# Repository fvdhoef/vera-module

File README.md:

# VERA module - Video Embedded Retro Adapter
This repository contains the files related to the VERA module. This module is developed for the Commander X16 computer by The 8-Bit Guy.

**NOTE**: The Commander X16 logo is part of the Commander X16 project and should not be used when the module is used with other projects.

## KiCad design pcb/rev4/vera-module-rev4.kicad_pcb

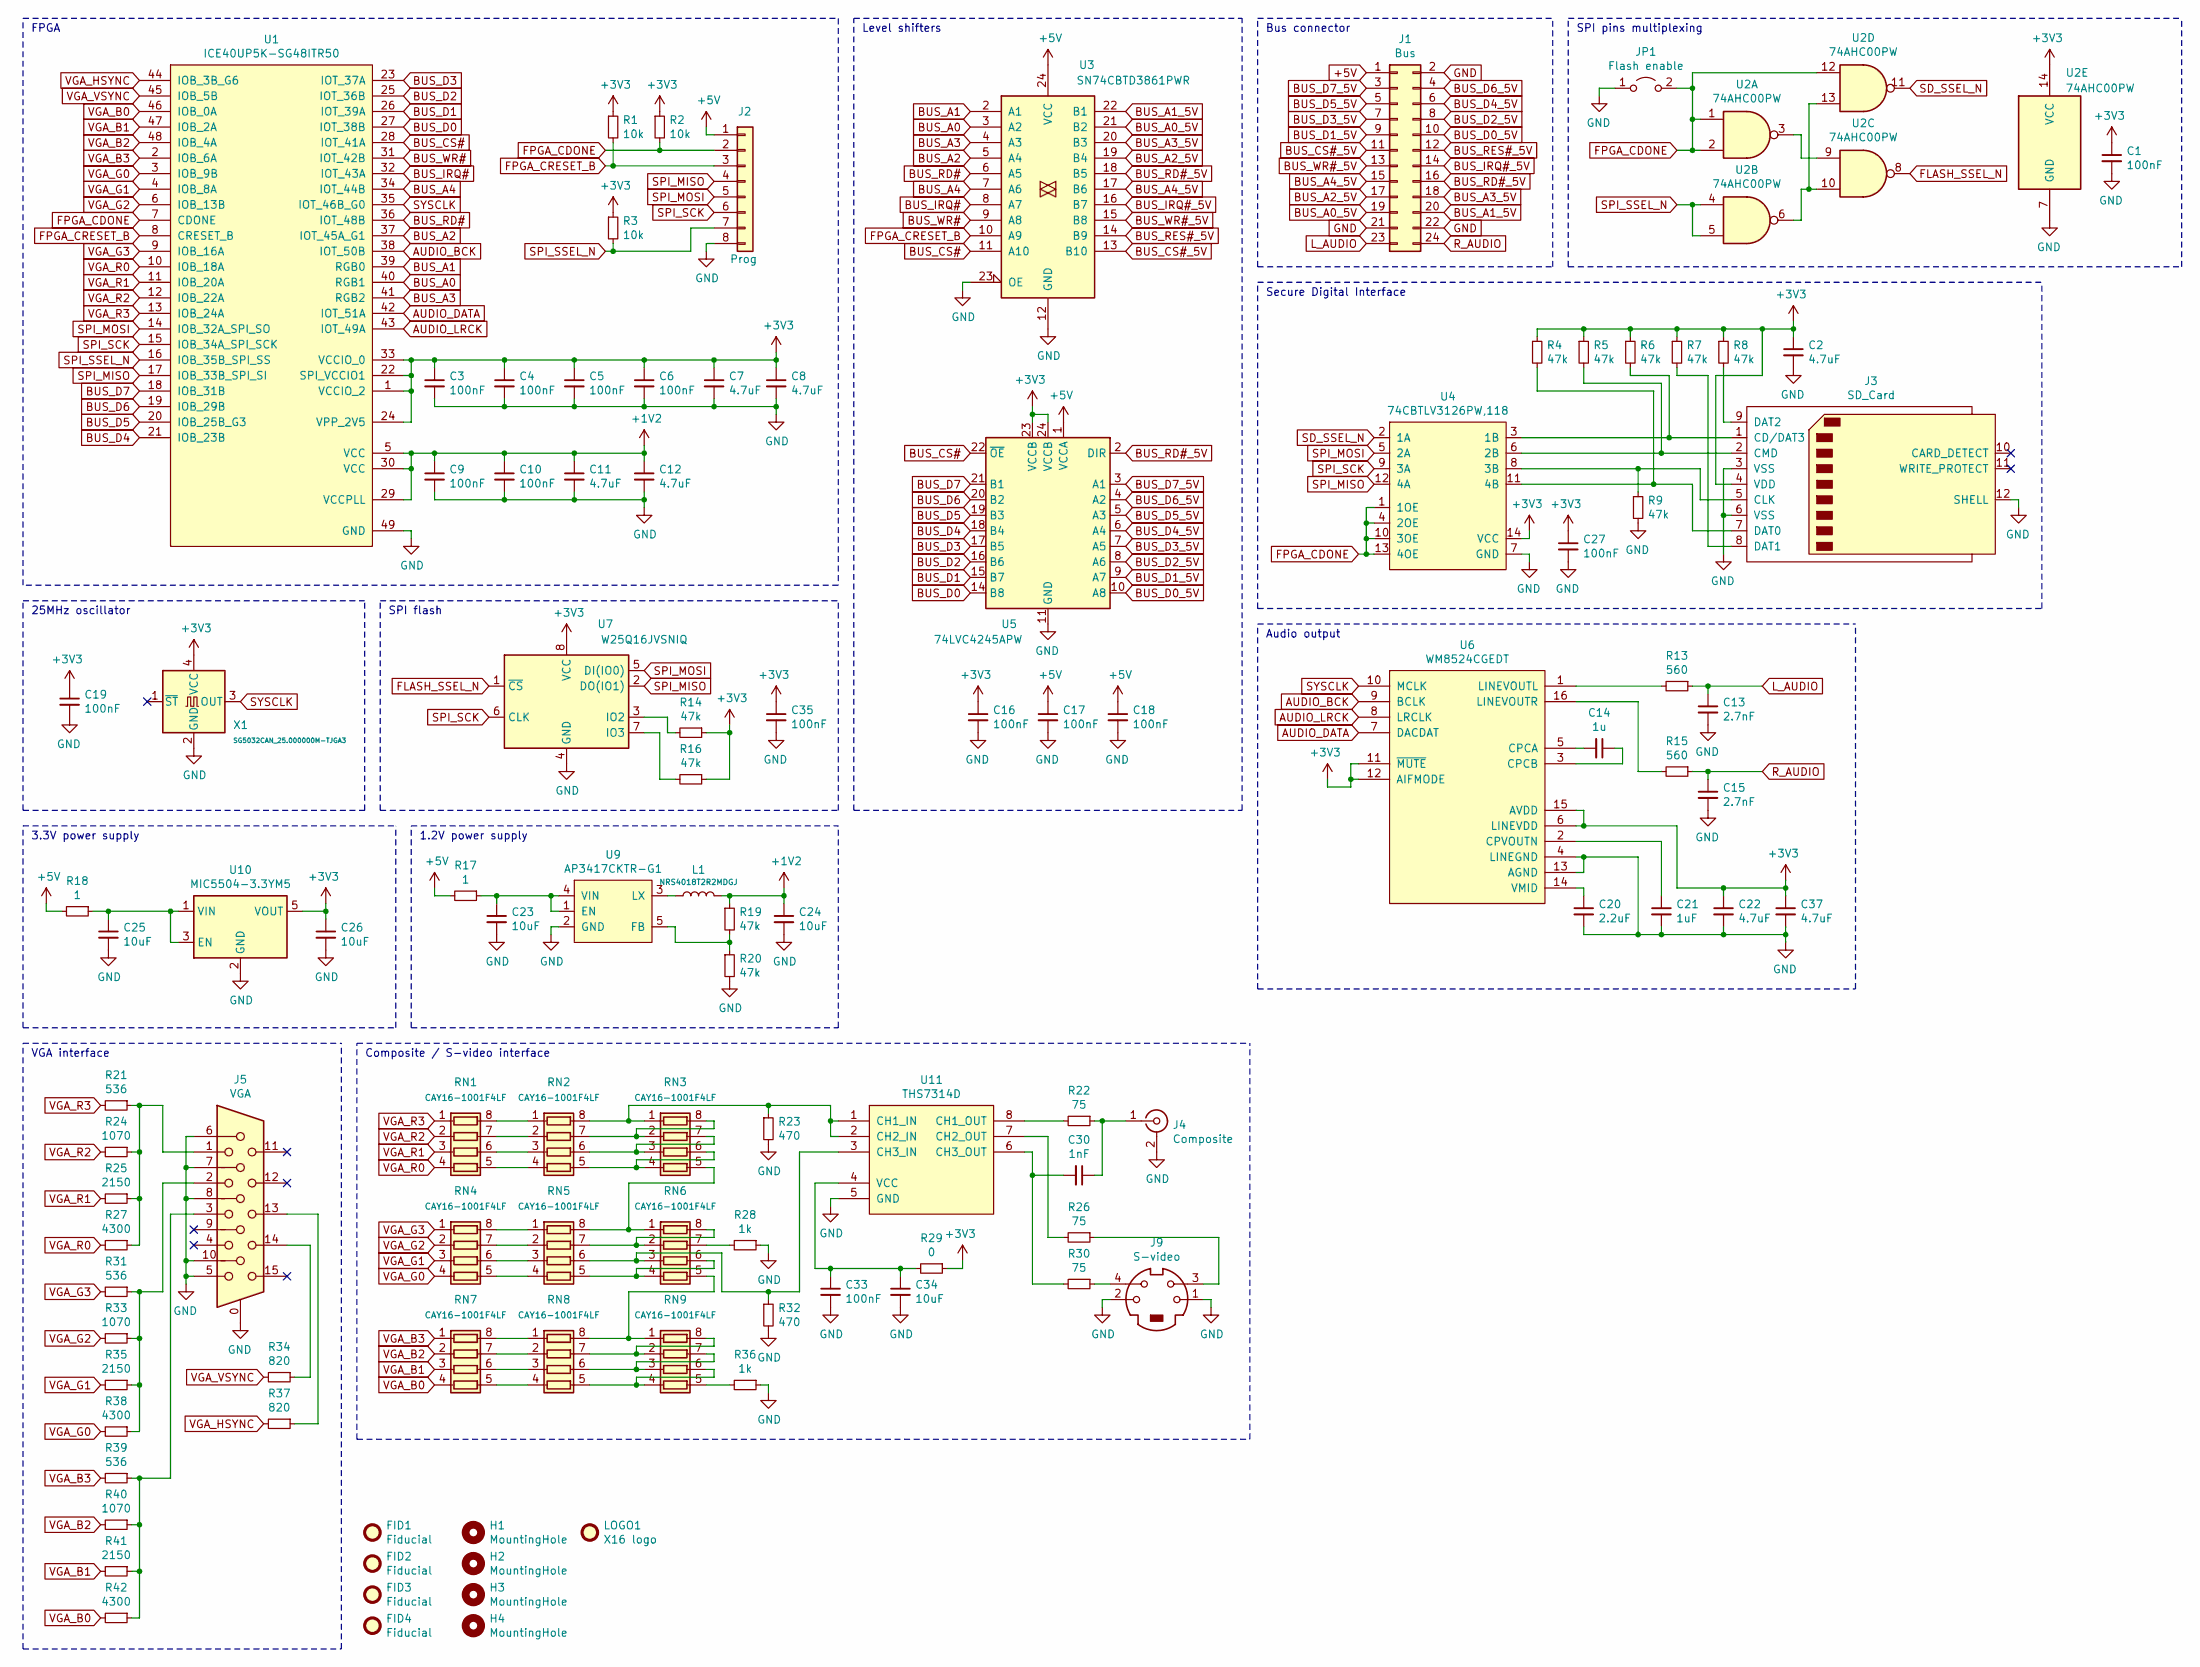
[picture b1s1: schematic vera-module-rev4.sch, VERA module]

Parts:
C1, C3, C4, C5, C6, C9, C10, C16, C17, C18, C19, C27, C33, C35: 100nF; C_0603_1608Metric
C2, C7, C8, C11, C12, C22, C37: 4.7uF; C_0603_1608Metric
C13, C15: 2.7nF; C_0603_1608Metric
C14: 1u; C_0603_1608Metric
C20: 2.2uF; C_0603_1608Metric
C21: 1uF; C_0603_1608Metric
C23, C24, C25, C26, C34: 10uF; C_0805_2012Metric
C30: 1nF; C_0603_1608Metric
FID1, FID2, FID3, FID4: Fiducial; Fiducial_1mm_Mask2mm
H1, H2, H3, H4: MountingHole; MountingHole_3.2mm_M3
J1: Bus; PinHeader_2x12_P2.54mm_Vertical
J2: Prog; PinHeader_1x08_P2.54mm_Vertical
J3: SD_Card; SD_TE_2041021
J4: Composite; RCJ-014
J5: VGA; ICD15S13E4GV00LF
J9: S-video; MD-40S
JP1: Flash enable; PinHeader_1x02_P2.54mm_Vertical
L1: NRS4018T2R2MDGJ; L_Bourns-SRN4018
LOGO1: X16 logo; x16plogo
R1, R2, R3: 10k; R_0603_1608Metric
R4, R5, R6, R7, R8, R9, R14, R16, R19, R20: 47k; R_0603_1608Metric
R13, R15: 560; R_0603_1608Metric
R17, R18: 1; R_0603_1608Metric
R21, R31, R39: 536; R_0603_1608Metric
R22, R26, R30: 75; R_0603_1608Metric
R23, R32: 470; R_0603_1608Metric
R24, R33, R40: 1070; R_0603_1608Metric
R25, R35, R41: 2150; R_0603_1608Metric
R27, R38, R42: 4300; R_0603_1608Metric
R28, R36: 1k; R_0603_1608Metric
R29: 0; R_0603_1608Metric
R34, R37: 820; R_0603_1608Metric
RN1, RN2, RN3, RN4, RN5, RN6, RN7, RN8, RN9: CAY16-1001F4LF; R_Array_Convex_4x0603
U1: ICE40UP5K-SG48ITR50; QFN-48-1EP_7x7mm_P0.5mm_EP5.3x5.3mm
U2: 74AHC00PW; TSSOP-14_4.4x5mm_P0.65mm
U3: SN74CBTD3861PWR; TSSOP-24_4.4x7.8mm_P0.65mm
U4: 74CBTLV3126PW,118; TSSOP-14_4.4x5mm_P0.65mm
U5: 74LVC4245APW; TSSOP-24_4.4x7.8mm_P0.65mm
U6: WM8524CGEDT; TSSOP-16_4.4x5mm_P0.65mm
U7: W25Q16JVSNIQ; SOIC-8_3.9x4.9mm_P1.27mm
U9: AP3417CKTR-G1; SOT-23-5
U10: MIC5504-3.3YM5; SOT-23-5
U11: THS7314D; SOIC-8_3.9x4.9mm_P1.27mm
X1: SG5032CAN_25.000000M-TJGA3; Oscillator_SMD_SeikoEpson_SG8002LB-4Pin_5.0x3.2mm

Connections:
+1V2: C9.1, C10.1, C11.1, C12.1, C24.1, L1.2, R19.1, U1.5 (VCC), U1.29 (VCCPLL), U1.30 (VCC)
+3V3: C1.1, C2.1, C3.1, C4.1, C5.1, C6.1, C7.1, C8.1, C16.1, C19.1, C22.1, C26.1, C27.1, C35.1, C37.1, J3.4 (VDD), R1.1, R2.1, R3.1, R4.1, R5.1, R6.1, R7.1, R8.1, R14.1, R16.1, R29.1, U1.1 (VCCIO_2), U1.22 (SPI_VCCIO1), U1.24 (VPP_2V5), U1.33 (VCCIO_0), U2.14 (VCC), U4.14 (VCC), U5.23 (VCCB), U5.24 (VCCB), U6.6 (LINEVDD), U6.11 (~MUTE), U6.12 (AIFMODE), U6.15 (AVDD), U7.8 (VCC), U10.5 (VOUT), X1.4 (VCC)
+5V: C17.1, C18.1, J1.1, J2.1, R17.2, R18.2, U3.24 (VCC), U5.1 (VCCA)
AUDIO_BCK: U1.38 (IOT_50B), U6.9 (BCLK)
AUDIO_DATA: U1.42 (IOT_51A), U6.7 (DACDAT)
AUDIO_LRCK: U1.43 (IOT_49A), U6.8 (LRCLK)
BUS_A0: U1.40 (RGB1), U3.3 (A2)
BUS_A0_5V: J1.19, U3.21 (B2)
BUS_A1: U1.39 (RGB0), U3.2 (A1)
BUS_A1_5V: J1.20, U3.22 (B1)
BUS_A2: U1.37 (IOT_45A_G1), U3.5 (A4)
BUS_A2_5V: J1.17, U3.19 (B4)
BUS_A3: U1.41 (RGB2), U3.4 (A3)
BUS_A3_5V: J1.18, U3.20 (B3)
BUS_A4: U1.34 (IOT_44B), U3.7 (A6)
BUS_A4_5V: J1.15, U3.17 (B6)
BUS_CS#: U1.28 (IOT_41A), U3.11 (A10), U5.22 (~OE)
BUS_CS#_5V: J1.11, U3.13 (B10)
BUS_D0: U1.27 (IOT_38B), U5.14 (B8)
BUS_D0_5V: J1.10, U5.10 (A8)
BUS_D1: U1.26 (IOT_39A), U5.15 (B7)
BUS_D1_5V: J1.9, U5.9 (A7)
BUS_D2: U1.25 (IOT_36B), U5.16 (B6)
BUS_D2_5V: J1.8, U5.8 (A6)
BUS_D3: U1.23 (IOT_37A), U5.17 (B5)
BUS_D3_5V: J1.7, U5.7 (A5)
BUS_D4: U1.21 (IOB_23B), U5.18 (B4)
BUS_D4_5V: J1.6, U5.6 (A4)
BUS_D5: U1.20 (IOB_25B_G3), U5.19 (B3)
BUS_D5_5V: J1.5, U5.5 (A3)
BUS_D6: U1.19 (IOB_29B), U5.20 (B2)
BUS_D6_5V: J1.4, U5.4 (A2)
BUS_D7: U1.18 (IOB_31B), U5.21 (B1)
BUS_D7_5V: J1.3, U5.3 (A1)
BUS_IRQ#: U1.32 (IOT_43A), U3.8 (A7)
BUS_IRQ#_5V: J1.14, U3.16 (B7)
BUS_RD#: U1.36 (IOT_48B), U3.6 (A5)
BUS_RD#_5V: J1.16, U3.18 (B5), U5.2 (DIR)
BUS_RES#_5V: J1.12, U3.14 (B9)
BUS_WR#: U1.31 (IOT_42B), U3.9 (A8)
BUS_WR#_5V: J1.13, U3.15 (B8)
FLASH_SSEL_N: U2.8, U7.1 (~CS)
FPGA_CDONE: J2.2, JP1.2 (B), R2.2, U1.7 (CDONE), U2.1, U2.2, U2.12, U4.1 (1OE), U4.4 (2OE), U4.10 (3OE), U4.13 (4OE)
FPGA_CRESET_B: J2.3, R1.2, U1.8 (CRESET_B), U3.10 (A9)
GND: C1.2, C2.2, C3.2, C4.2, C5.2, C6.2, C7.2, C8.2, C9.2, C10.2, C11.2, C12.2, C13.2, C15.2, C16.2, C17.2, C18.2, C19.2, C20.2, C21.2, C22.2, C23.2, C24.2, C25.2, C26.2, C27.2, C33.2, C34.2, C35.2, C37.2, J1.2, J1.21, J1.22, J2.8, J3.3 (VSS), J3.6 (VSS), J3.12 (SHELL), J4.2 (Ext), J5.0, J5.5, J5.6, J5.7, J5.8, J5.10, J9.1, J9.2, JP1.1 (A), R9.2, R20.2, R23.2, R28.1, R32.2, R36.1, U1.49 (GND), U2.7 (GND), U3.12 (GND), U3.23 (OE), U4.7 (GND), U5.11 (GND), U5.12 (GND), U5.13 (GND), U6.4 (LINEGND), U6.13 (AGND), U7.4 (GND), U9.2 (GND), U10.2 (GND), U11.5 (GND), X1.2 (GND)
L_AUDIO: C13.1, J1.23, R13.1
unnamed: C14.1, U6.3 (CPCB)
unnamed: C14.2, U6.5 (CPCA)
unnamed: C20.1, U6.14 (VMID)
unnamed: C21.1, U6.2 (CPVOUTN)
unnamed: C23.1, R17.1, U9.1 (EN), U9.4 (VIN)
unnamed: C25.1, R18.1, U10.1 (VIN), U10.3 (EN)
unnamed: C30.1, J4.1 (In), R22.1
unnamed: C30.2, R30.2, U11.6 (CH3_OUT)
unnamed: C33.1, C34.1, R29.2, U11.4 (VCC)
unnamed: J3.1 (CD/DAT3), R6.2, U4.3 (1B)
unnamed: J3.2 (CMD), R5.2, U4.6 (2B)
unnamed: J3.5 (CLK), R9.1, U4.8 (3B)
unnamed: J3.7 (DAT0), R4.2, U4.11 (4B)
unnamed: J3.8 (DAT1), R7.2
unnamed: J3.9 (DAT2), R8.2
unnamed: J5.1, R21.1, R24.1, R25.1, R27.1
unnamed: J5.2, R31.1, R33.1, R35.1, R38.1
unnamed: J5.3, R39.1, R40.1, R41.1, R42.1
unnamed: J5.13, R37.1
unnamed: J5.14, R34.1
unnamed: J9.3, R26.1
unnamed: J9.4, R30.1
unnamed: L1.1, U9.3 (LX)
unnamed: R13.2, U6.1 (LINEVOUTL)
unnamed: R14.2, U7.3 (IO2)
unnamed: R15.2, U6.16 (LINEVOUTR)
unnamed: R16.2, U7.7 (IO3)
unnamed: R19.2, R20.1, U9.5 (FB)
unnamed: R22.2, U11.8 (CH1_OUT)
unnamed: R23.1, RN2.8 (R1.2), RN3.1 (R1.1), U11.1 (CH1_IN), U11.2 (CH2_IN)
unnamed: R26.2, U11.7 (CH2_OUT)
unnamed: R28.2, RN6.7 (R2.2)
unnamed: R32.1, RN5.6 (R3.2), RN6.3 (R3.1), U11.3 (CH3_IN)
unnamed: R36.2, RN9.5 (R4.2)
unnamed: RN1.5 (R4.2), RN2.4 (R4.1)
unnamed: RN1.6 (R3.2), RN2.3 (R3.1)
unnamed: RN1.7 (R2.2), RN2.2 (R2.1)
unnamed: RN1.8 (R1.2), RN2.1 (R1.1)
unnamed: RN2.5 (R4.2), RN3.4 (R4.1), RN3.6 (R3.2)
unnamed: RN2.6 (R3.2), RN3.3 (R3.1), RN3.7 (R2.2)
unnamed: RN2.7 (R2.2), RN3.2 (R2.1), RN3.8 (R1.2)
unnamed: RN3.5 (R4.2), RN5.8 (R1.2), RN6.1 (R1.1)
unnamed: RN4.5 (R4.2), RN5.4 (R4.1)
unnamed: RN4.6 (R3.2), RN5.3 (R3.1)
unnamed: RN4.7 (R2.2), RN5.2 (R2.1)
unnamed: RN4.8 (R1.2), RN5.1 (R1.1)
unnamed: RN5.5 (R4.2), RN6.4 (R4.1), RN6.6 (R3.2)
unnamed: RN5.7 (R2.2), RN6.2 (R2.1), RN6.8 (R1.2)
unnamed: RN6.5 (R4.2), RN8.8 (R1.2), RN9.1 (R1.1)
unnamed: RN7.5 (R4.2), RN8.4 (R4.1)
unnamed: RN7.6 (R3.2), RN8.3 (R3.1)
unnamed: RN7.7 (R2.2), RN8.2 (R2.1)
unnamed: RN7.8 (R1.2), RN8.1 (R1.1)
unnamed: RN8.5 (R4.2), RN9.4 (R4.1), RN9.6 (R3.2)
unnamed: RN8.6 (R3.2), RN9.3 (R3.1), RN9.7 (R2.2)
unnamed: RN8.7 (R2.2), RN9.2 (R2.1), RN9.8 (R1.2)
unnamed: U2.3, U2.9
unnamed: U2.6, U2.10, U2.13
R_AUDIO: C15.1, J1.24, R15.1
SD_SSEL_N: U2.11, U4.2 (1A)
SPI_MISO: J2.4, U1.17 (IOB_33B_SPI_SI), U4.12 (4A), U7.2 (DO(IO1))
SPI_MOSI: J2.5, U1.14 (IOB_32A_SPI_SO), U4.5 (2A), U7.5 (DI(IO0))
SPI_SCK: J2.6, U1.15 (IOB_34A_SPI_SCK), U4.9 (3A), U7.6 (CLK)
SPI_SSEL_N: J2.7, R3.2, U1.16 (IOB_35B_SPI_SS), U2.4, U2.5
SYSCLK: U1.35 (IOT_46B_G0), U6.10 (MCLK), X1.3 (OUT)
VGA_B0: R42.2, RN7.4 (R4.1), U1.46 (IOB_0A)
VGA_B1: R41.2, RN7.3 (R3.1), U1.47 (IOB_2A)
VGA_B2: R40.2, RN7.2 (R2.1), U1.48 (IOB_4A)
VGA_B3: R39.2, RN7.1 (R1.1), U1.2 (IOB_6A)
VGA_G0: R38.2, RN4.4 (R4.1), U1.3 (IOB_9B)
VGA_G1: R35.2, RN4.3 (R3.1), U1.4 (IOB_8A)
VGA_G2: R33.2, RN4.2 (R2.1), U1.6 (IOB_13B)
VGA_G3: R31.2, RN4.1 (R1.1), U1.9 (IOB_16A)
VGA_HSYNC: R37.2, U1.44 (IOB_3B_G6)
VGA_R0: R27.2, RN1.4 (R4.1), U1.10 (IOB_18A)
VGA_R1: R25.2, RN1.3 (R3.1), U1.11 (IOB_20A)
VGA_R2: R24.2, RN1.2 (R2.1), U1.12 (IOB_22A)
VGA_R3: R21.2, RN1.1 (R1.1), U1.13 (IOB_24A)
VGA_VSYNC: R34.2, U1.45 (IOB_5B)

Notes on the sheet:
FPGA
25MHz oscillator
Level shifters
Bus connector
Secure Digital Interface
3.3V power supply
1.2V power supply
VGA interface
Composite / S-video interface
Audio output
SPI flash
SPI pins multiplexing

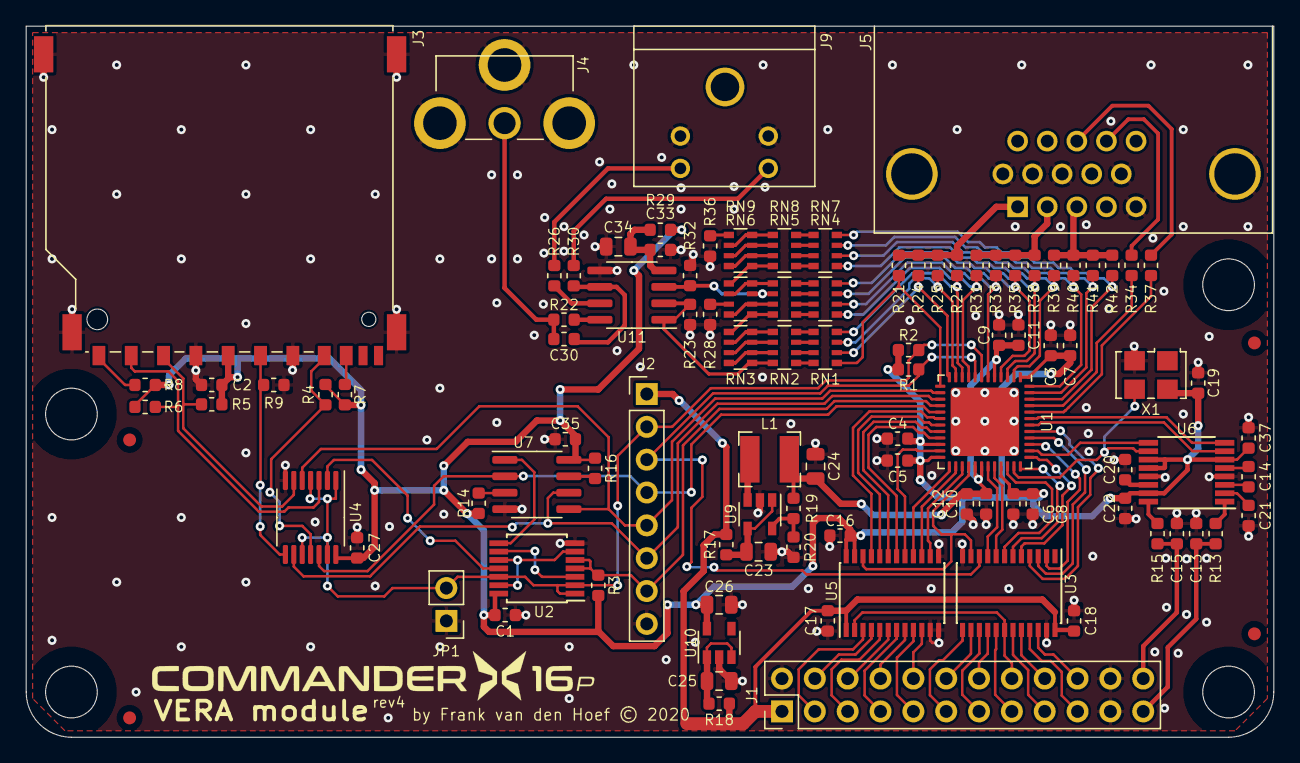
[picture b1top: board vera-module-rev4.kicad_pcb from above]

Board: 2 copper layers, 96.5 x 55.0 mm, 108 parts (0 on the bottom side), 125 nets.

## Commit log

2019-06-23 Initial commit.
2019-06-26 Initial FPGA code.
2019-06-26 Adding code for FPGA programmer. Adding character ROM.
2019-06-29 Fixing clock of FPGA programmer.
2019-06-30 Adding 6502 datasheet.
2019-06-30 Worked on bus interface.
2019-07-02 Another try.
2019-07-03 Fixed extbus interface.
2019-07-03 Worked on graphics module.
2019-07-05 Restructured top level.
2019-07-05 Pipeline compensation in VGA output.
2019-07-06 Worked on layer renderer.
2019-07-06 Fix in renderer.
2019-07-06 Text mode is working.
2019-07-06 Updated document.
2019-07-10 Added power-on-reset counter.
2019-07-14 Working on NTSC composite video.
2019-07-15 Added composite video top level.
2019-07-17 Improved external bus interface
2019-07-20 Fixes for release to Kevin.
2019-07-20 Working on modes.
2019-07-24 Working on video modes.
2019-07-28 Implemented bootloader for test system.
2019-07-28 Fixed vertical scrolling. Improved bus interface.
2019-07-28 Fixing 2bpp/4bpp tile modes.
2019-07-29 Fixed issue in external bus interface.
2019-07-30 8bpp tile mode is working
2019-07-31 Implemented V-flip.
2019-07-31 Implemented H-flip
2019-07-31 Implemented bitmap modes.
2019-08-02 Changed address bus width of layer renderer from 18-bit to 16 bit.
2019-08-02 Moved PCB layout to rev0 directory.
2019-08-02 Worked on rev1 PCB.
2019-08-03 Added initial composer.
2019-08-03 Worked on rev1 board.
2019-08-03 Implemented font inversion in logic instead of ROM to save memory.
2019-08-10 Fixed v-sync interrupt.
2019-08-11 Working on sprite support.
2019-08-12 Restructured design using line counter. Composite mode working.
2019-08-12 Added simultaneous support for VGA and composite.
2019-08-13 Added RGB video output.
2019-08-13 Implemented horizontal scaling.
2019-08-13 Implemented fractional vertical scaling.
2019-08-14 Implemented active display area and border.
2019-08-15 Working on sprite renderer.
2019-08-16 Fixing erasing of sprite line buffer.
2019-08-16 Sprite renderer: implemented z priority.
2019-08-17 Fixed off-by-one line rendering issue in composer.
2019-08-17 Sprite flipping is working.
2019-08-21 Line interrupt and sprite collision detection implemented.
2019-08-26 Finished work on rev1 VERA PCB.
2019-08-27 Adding some documents.
2019-08-27 Disabling RDY for now.
2019-08-27 Restructured layer line buffers, freeing up 2 block RAMs.
2019-08-30 Missing file in radiant.
2019-09-04 Renamed PHY2 to PHI2. Added missing inits on reset.
2019-09-04 New sprite attribute ram layout.
2019-09-04 0.7 release.
2019-09-07 Missing checkin.
2019-09-07 Changes for rev1.
2019-09-08 Cleaning up.
2019-09-08 Working on VERA generating bus clock.
2019-09-08 Working at 3.125MHz.
2019-09-11 Running at 6.25MHz.
2019-09-11 Improving extbusif.
2019-09-11 Improving busif.
2019-09-11 Running stable at 8.33MHz.
2019-09-11 Reorganizing project directory.
2019-09-11 Fixed composite mode.
2019-09-11 Added UART interface.
2019-09-14 Reorganized project directory.
2019-09-14 Reorganized address space.
2019-09-14 Reorganized bus interface to match rev1 more.
2019-09-14 Reordered external bus registers. Power-of-2 increment values.
2019-09-14 Updated to 0.8.
2019-09-14 Improving stability of extbus interface.
2019-09-14 Added SPI controller.
2019-09-15 v0.8 changes.
2019-09-15 Removed character ROM.
2019-09-18 Moved busy bit of spi controller to bit 7.
2019-09-18 Implemented x16load program.
2019-09-22 Working on audio.
2019-09-22 Implemented PHI2 clock speed control.
2020-02-14 VERA module rev2 PCB.
2020-02-15 Rev2 PCB: added X16 logo.
2020-02-18 vera rev2 pcb: Increased mounting holes to 4mm.
2020-02-29 Adding missing binaries.
2020-03-01 Reorganizing code.
2020-03-03 New bus interface works on real hardware!
2020-03-04 Improved register interface.
2020-03-04 Worked on rev3 PCB.
2020-03-06 Worked on audio.
2020-03-06 Updated increments for bitmap modes. Implemented increment toggle.
2020-03-08 Fixes.
2020-03-08 Implemented PCM audio.
2020-03-09 Adding address decrement. Fixing port 1 address increment.
2020-03-11 Fix in vram interface.
2020-03-13 Fixed issue with spurious chip selects.
2020-03-13 Fixing 1bpp bitmap mode. Fixing PSG frequency step.
2020-03-14 Implemented spi 'slow' bit.
2020-03-14 Test programs.
2020-03-15 Updated test programs to ca65.
2020-03-18 Working on SD card.
2020-03-18 SD card writing.
2020-03-19 Working on FAT32.
2020-03-22 FAT32
2020-03-23 Cleaning up code.
2020-03-23 Clean up.
2020-03-24 Implemented context switching
2020-03-25 Text display code.
2020-03-26 Font tweaks.
2020-03-26 More font tweaks.
2020-03-26 Working on command interpreter.
2020-03-28 Reorganized files.
2020-03-28 Directory changing working.
2020-03-28 Cleanup.
2020-03-28 CLI.
2020-03-29 Directory listing now in lower case. Working on rename.
2020-03-29 Replacing unnamed labels in macros with local labels.
2020-03-29 File rename is working.
2020-03-30 Working on delete command.
2020-03-30 Prevent loading an already loaded sector.
2020-04-01 Handle second FAT writes.
2020-04-01 Implemented sector read/write optimization.
2020-04-05 Implemented find_free_cluster function.
2020-04-05 Working on creating file.
2020-04-05 Implemented fat32_create.
2020-04-07 Initial file write code.
2020-04-08 Improved 'dir' command.
2020-04-08 Keep track of free clusters.
2020-04-08 Fixing issues.
2020-04-08 Working on write code.
2020-04-10 Allocate new clusters while writing.
2020-04-10 Adding copyright notices.
2020-04-11 SD card handling improvements.
2020-04-12 Zero out allocated directory clusters.
2020-04-12 Free cluster search improvement.
2020-04-12 Optimizing SD card reading/writing.
2020-04-12 Optimized SD card code.
2020-04-12 SD card driver LBA is now little endian.
2020-04-12 Fixing issues on real hardware.
2020-04-12 Added some missing error handling.
2020-04-12 Moving sector buffer to sdcard.s.
2020-04-13 Optimizing error paths.
2020-04-13 Slight optimization in fat32_write_byte.
2020-04-13 Clean up in fat32_write_byte.
2020-04-13 Fix update of file size on write.
2020-04-13 Implemented fat32_write.
2020-04-13 Clear BSS to fix all weird problems.
2020-04-13 Initialize cwd_cluster.
2020-04-13 Fixing bug in fat32_write.
2020-04-14 Implemented fat32_read.
2020-04-14 Read speed improvements.
2020-04-15 FPGA: implemented auto-rx mode in SPI controller.
2020-04-15 Implemented auto-rx mode in SD card code.
2020-04-15 Implemented movie player.
2020-04-15 Fixing warnings.
2020-04-16 FPGA cleanup.
2020-04-16 Improving write speed.
2020-04-17 Implemented fat32_mkdir.
2020-04-17 Implemented fat32_rmdir.
2020-04-18 Fix in fat32_set_context.
2020-04-18 Implemented copy command.
2020-07-04 Worked on VERA rev4.
2020-07-04 Adding rev4 zip.
2020-07-13 Adding jump table and test app.
2020-07-13 VERA init code.
2020-07-13 Adding executable header.
2020-07-13 Started work on fos-rom.
2020-07-13 Initial NMI based PS/2 support.
2020-07-13 Changes for rev3/rev4.
2020-07-13 Adding rev4 binary.
2022-03-14 Create LICENSE
2022-03-14 Updating readme.
2022-03-14 Adding programmer's reference.
2022-04-02 Change register index values to match their index on VERA's address bus.
2022-04-03 Sample rdaddr_r at the rising edge of bus_edge
2022-04-03 Remove duplicate reference doc.
2022-04-26 Fix sprite rendering priority; earlier sprites get priority over later ones
2022-04-27 Corrected error causing only transparent pixels to be drawn.
2022-06-21 Fix for line irq's firing twice when IRQ_LINE <= 10.
2022-08-31 Plumbed fifo_empty signal up to top and added it to bit 6 of register 0x1B.
2022-08-31 Added documentation for FIFO empty bit.
2022-09-17 HDMI Initial Commit
2022-09-20 Roll back unrelated change to rdaddr_r sampling.
2022-09-20 Return line index value instead of line irq value in register $08 (and bit 7 of $06)
2022-09-20 Fix tile offset calculation causing issue #17
2022-09-20 Sample the address and data bus earlier during writes.
2022-09-21 line_idx was scaled and did not indicate true line scanline. Plumbed y_counter_rr up to top and use that instead.
2022-09-21 Document functionality of scanline register.
2022-09-21 Cleaned up documentation wording a bit.
2022-09-21 Remove scare quotes.
2022-09-25 Implemented composite vblank irq fix for #7 from akumanatt.
2022-10-07 Fix tile address calculation for 16-pixel wide 1bpp tiles.
2022-10-07 Move SCANLINE[8] to IEN[6] and restore IRQLINE[8] to IEN[7]
2022-10-12 Increase audio mixing reolution
    and reset PSG phase when output is disabled
2022-10-14 Forgot to add this change
2022-10-25 Interlaced line irq fixed; signal name error in IEN register fixed
2023-01-14 Scanline bit 8 comes out of bit 6 of IEN (PR#25)
2023-01-21 added write byte pattern feature: write multiple bytes with the same value in a certain value
2023-01-21 attempt to add a 32-bit cache for 'blitting'
2023-01-21 cleaner version of blitter, condition now in clocked block
2023-01-22 added two 32-bit data0/1 regs and 32-bit cache reg in top.v instead.
2023-01-26 cleanup tabs and more robust check to fill cache
2023-01-26 cleanup: removed unused register
2023-01-26 making sure shadow VRAM (for PSG/Palette/Sprites) is not multibyte written to or read from
2023-01-26 Fix sprite collision and improve write timings (again)
2023-01-27 enabled nibble based masking during blit. Reordered the write pattern mapping
2023-01-28 Added an explanation of multibyte write and copy
2023-01-28 Improved wording in explanation
2023-02-23 Fix PCM volume scaling
2023-02-23 Make *2 part of the volume table
2023-03-16 Make VGA sync polarity negative.
2023-03-16 Draw black pixels outside of active display.
2023-03-17 Enable 240p mode with bit 3 of DC_VIDEO.
2023-10-20 Fixing compilation issue.

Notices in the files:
pcb/rev4/vera-module-rev4.kicad_pcb:
by Frank van den Hoef © 2020
pcb/rev4/vera-module-rev4.sch:
(C) 2020 Frank van den Hoef
